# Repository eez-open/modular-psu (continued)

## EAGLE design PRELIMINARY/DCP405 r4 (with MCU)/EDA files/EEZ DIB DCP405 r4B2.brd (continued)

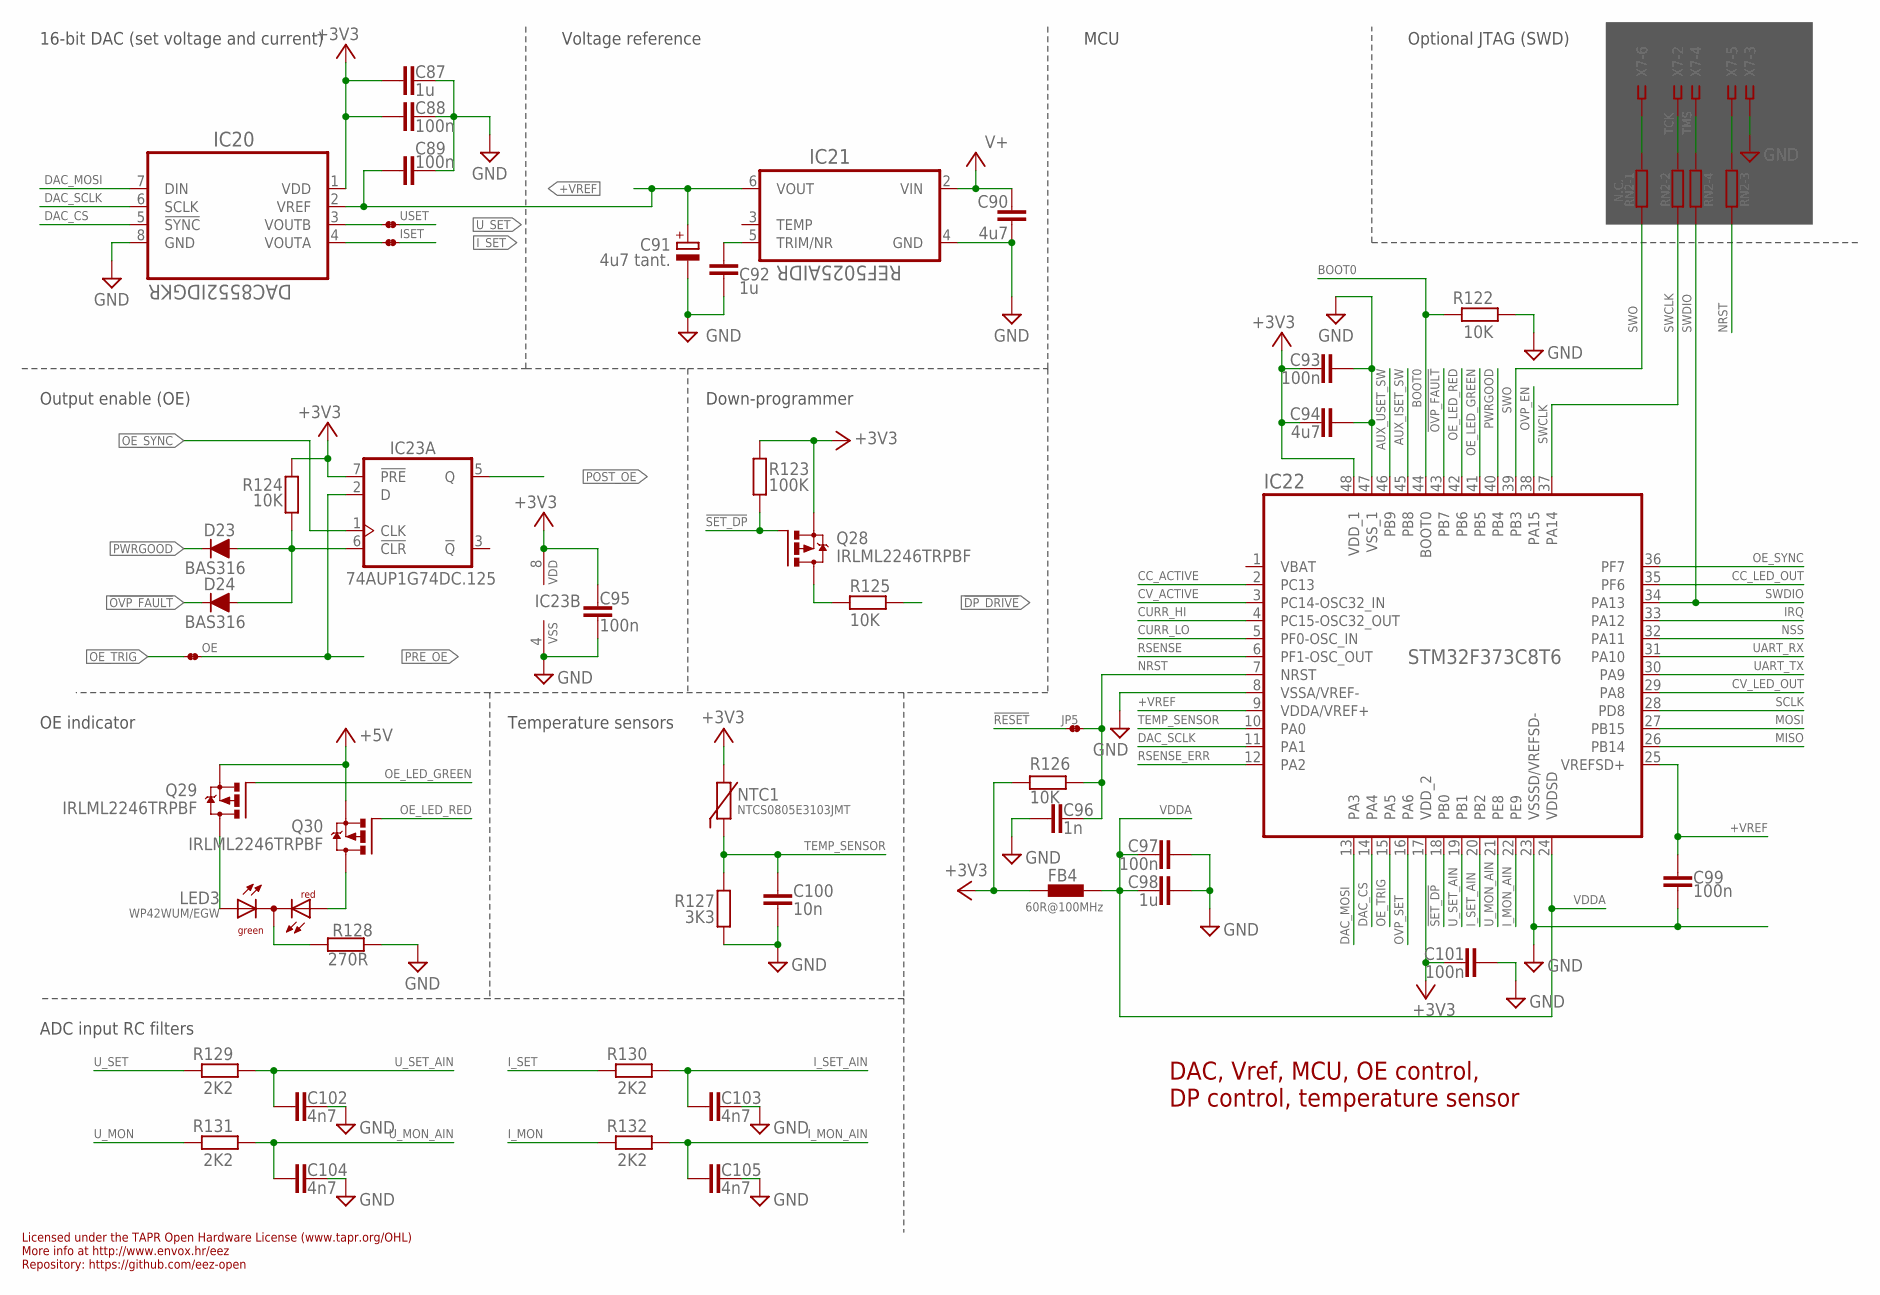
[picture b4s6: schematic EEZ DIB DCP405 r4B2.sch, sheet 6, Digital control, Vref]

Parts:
C87, C92, C98: 1u; C0805
C88, C89, C93, C95, C97, C99, C101: 100n; C0603
C90, C94: 4u7; C1206
C91: 4u7 tant.; EC1206
C96: 1n; C0805
C100: 10n; C0805
C102, C103, C104, C105: 4n7; C0805
D23, D24: BAS316; SOD323-R
FB4: 60R@100MHz; BEAD0603
IC20: DAC8552IDGKR; DGK8-M
IC21: REF5025AIDR; SOIC127P600X175-8N
IC22: STM32F373C8T6; LQFP-48
IC23: 74AUP1G74DC.125; DCU8
ISET: JP2-NOCUT-0805; JP2-0805-NOCUT
JP5: JP2-NOCUT-0805; JP2-0805-NOCUT
LED3: WP42WUM/EGW; L-42WUM-1EGWT
NTC1: NTCS0805E3103JMT; R_0805
OE: JP2-NOCUT-0805; JP2-0805-NOCUT
Q28, Q29, Q30: IRLML2246TRPBF; SOT95P237X112-3N
R122, R124, R125, R126: 10K; R0805
R123: 100K; R0805
R127: 3K3; R0805
R128: 270R; R0805
R129, R130, R131, R132: 2K2; R0805
RN2: N.C.; CAY16
USET: JP2-NOCUT-0805; JP2-0805-NOCUT
X7: N.C.; SSW-106-02-S-S

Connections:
!DP_DRIVE: R125.1; also elsewhere on the board
!OVP_FAULT: D24.C, IC22.43 (PB7); also elsewhere on the board
!RESET: JP5.1; also elsewhere on the board
!SET_DP: IC22.18 (PB0), Q28.1 (G), R123.2
+3V3: C87.1, C88.2, C93.2, C94.1, C95.2, C101.2, FB4.P$1 (1), IC20.1 (VDD), IC22.17 (VDD_2), IC22.48 (VDD_1), IC23.7 (!PRE), IC23.8 (VDD), NTC1.1, Q28.2 (S), R123.1, R124.1, R126.1; also elsewhere on the board
+5V: Q29.2 (S), Q30.2 (S); also elsewhere on the board
+VREF: C89.2, C91.+, C99.2, IC20.2 (VREF), IC21.6 (VOUT), IC22.9 (VDDA/VREF+), IC22.25 (VREFSD+); also elsewhere on the board
AUX_ISET_SW: IC22.45 (PB8); also elsewhere on the board
AUX_USET_SW: IC22.46 (PB9); also elsewhere on the board
BOOT0: IC22.44 (BOOT0), R122.2; also elsewhere on the board
CC_ACTIVE: IC22.2 (PC13); also elsewhere on the board
CC_LED_OUT: IC22.35 (PF6); also elsewhere on the board
CURR_HI: IC22.4 (PC15-OSC32_OUT); also elsewhere on the board
CURR_LO: IC22.5 (PF0-OSC_IN); also elsewhere on the board
CV_ACTIVE: IC22.3 (PC14-OSC32_IN); also elsewhere on the board
CV_LED_OUT: IC22.29 (PA8); also elsewhere on the board
DAC_CS: IC20.5 (!SYNC), IC22.14 (PA4)
DAC_MOSI: IC20.7 (DIN), IC22.13 (PA3)
DAC_SCLK: IC20.6 (SCLK), IC22.11 (PA1)
DP_LED: Q28.3 (D), R125.2
GND: C87.2, C88.1, C89.1, C90.2, C91.-, C92.2, C93.1, C94.2, C95.1, C96.2, C97.1, C98.1, C99.1, C100.1, C101.1, C102.1, C103.1, C104.1, C105.1, IC20.8 (GND), IC21.4 (GND), IC22.8 (VSSA/VREF-), IC22.23 (VSSSD/VREFSD-), IC22.47 (VSS_1), IC23.4 (VSS), R122.1, R127.2, R128.2, X7.3; also elsewhere on the board
IRQ: IC22.33 (PA12); also elsewhere on the board
I_MON: R132.2; also elsewhere on the board
I_MON_AIN: C105.2, IC22.22 (PE9), R132.1
I_SET: ISET.2, R130.2; also elsewhere on the board
I_SET_AIN: C103.2, IC22.20 (PB2), R130.1
MISO: IC22.26 (PB14); also elsewhere on the board
MOSI: IC22.27 (PB15); also elsewhere on the board
unnamed: LED3.CC (C), R128.1
unnamed: LED3.RED (AR), Q30.3 (D)
unnamed: LED3.GREEN (AG), Q29.3 (D)
unnamed: IC20.3 (VOUTB), USET.1
unnamed: IC20.4 (VOUTA), ISET.1
unnamed: D23.A, D24.A, IC23.6 (!CLR), R124.2
unnamed: C92.1, IC21.5 (TRIM/NR)
unnamed: RN2.8 (2), X7.6
unnamed: RN2.6 (2), X7.5
NRST: C96.1, IC22.7 (NRST), JP5.2, R126.2, RN2.3 (1)
NSS: IC22.32 (PA11); also elsewhere on the board
OE_LED_GREEN: IC22.41 (PB5), Q29.1 (G)
OE_LED_RED: IC22.42 (PB6), Q30.1 (G)
OE_SYNC: IC22.36 (PF7), IC23.1 (CLK); also elsewhere on the board
OE_TRIG: IC22.15 (PA5), OE.1
OVP_EN: IC22.38 (PA15); also elsewhere on the board
OVP_SET: IC22.16 (PA6); also elsewhere on the board
POST_OE: IC23.5 (Q); also elsewhere on the board
PRE_OE: IC23.2 (D), OE.2; also elsewhere on the board
PWRGOOD: D23.C, IC22.40 (PB4); also elsewhere on the board
RSENSE: IC22.6 (PF1-OSC_OUT); also elsewhere on the board
RSENSE_ERR: IC22.12 (PA2); also elsewhere on the board
SCLK: IC22.28 (PD8); also elsewhere on the board
SWCLK: IC22.37 (PA14), RN2.2 (1)
SWDIO: IC22.34 (PA13), RN2.4 (1)
SWO: IC22.39 (PB3), RN2.1
TCK: RN2.7 (2), X7.2
TEMP_SENSOR: C100.2, IC22.10 (PA0), NTC1.2, R127.1
TMS: RN2.5 (2), X7.4
UART_RX: IC22.31 (PA10); also elsewhere on the board
UART_TX: IC22.30 (PA9); also elsewhere on the board
U_MON: R131.2; also elsewhere on the board
U_MON_AIN: C104.2, IC22.21 (PE8), R131.1
U_SET: R129.2, USET.2; also elsewhere on the board
U_SET_AIN: C102.2, IC22.19 (PB1), R129.1
V+: C90.1, IC21.2 (VIN); also elsewhere on the board
VDDA: C97.2, C98.2, FB4.P$2 (2), IC22.24 (VDDSD)

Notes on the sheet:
16-bit DAC (set voltage and current)
Voltage reference
Licensed under the TAPR Open Hardware License (www.tapr.org/OHL)
Repository: https://github.com/eez-open
More info at http://www.envox.hr/eez
DAC, Vref, MCU, OE control, DP control, temperature sensor
Down-programmer
Optional JTAG (SWD)
MCU
ADC input RC filters
Temperature sensors
Output enable (OE)
OE indicator

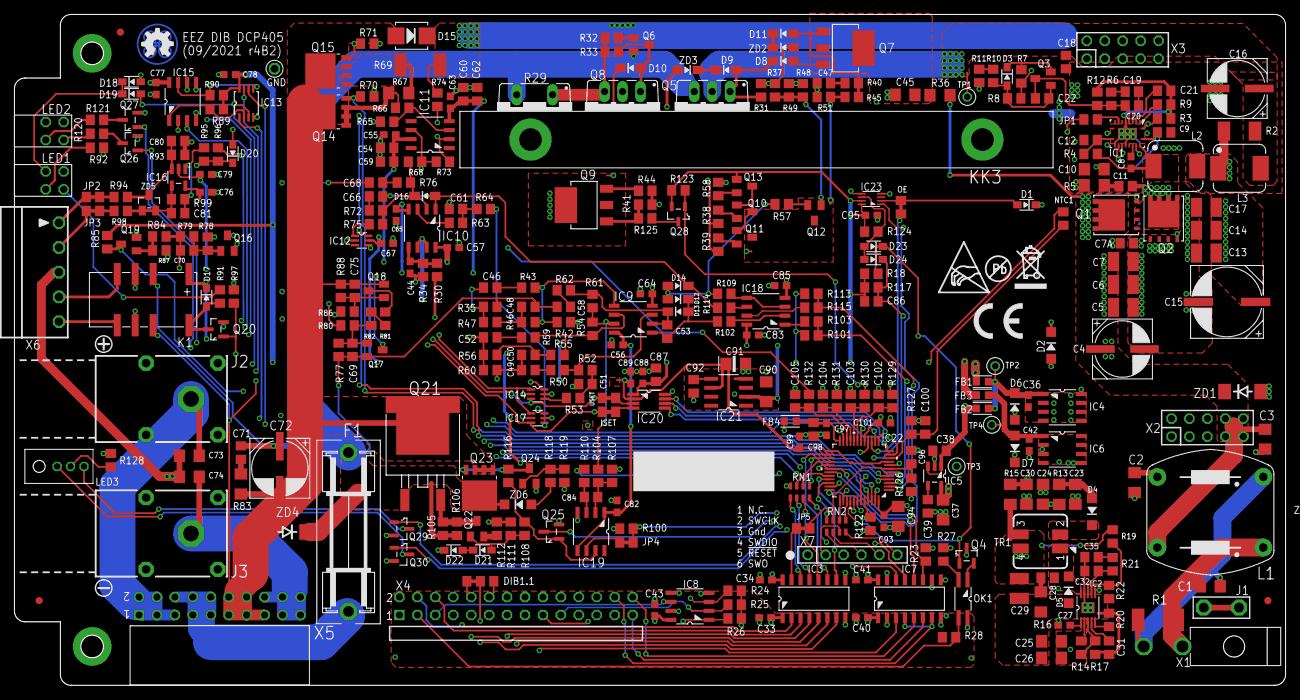
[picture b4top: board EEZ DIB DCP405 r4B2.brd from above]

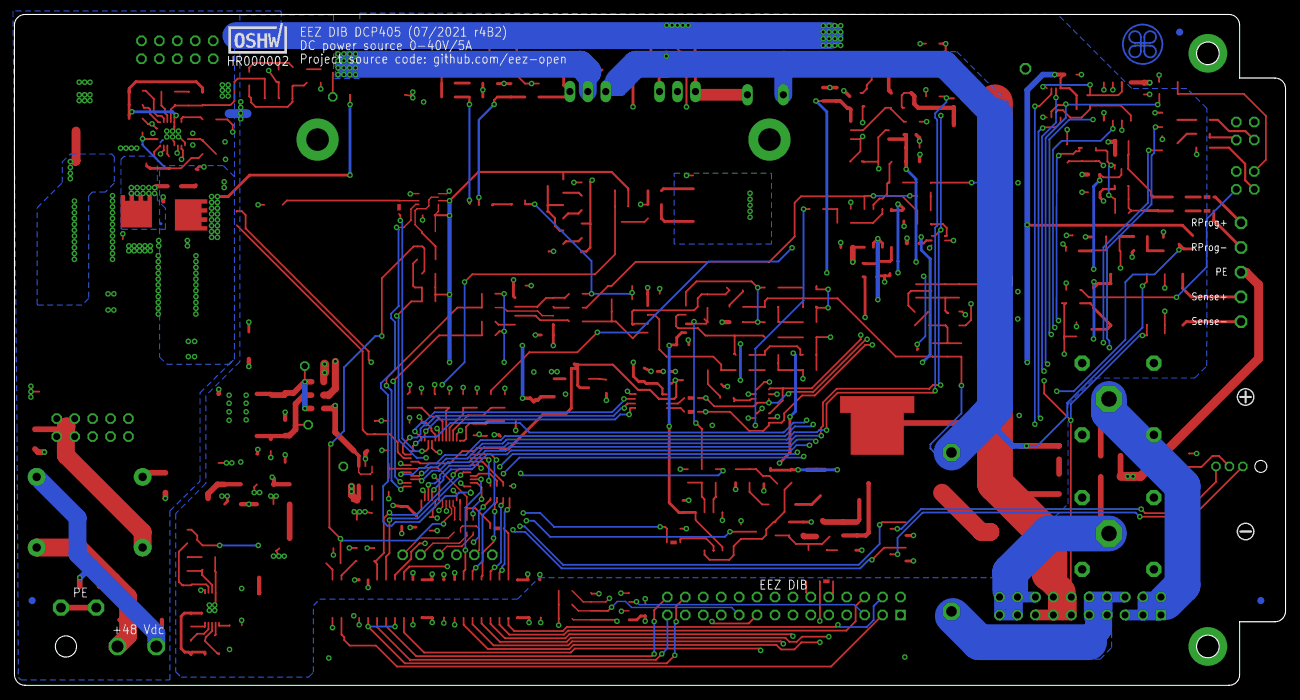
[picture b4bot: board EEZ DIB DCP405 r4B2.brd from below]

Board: 4 copper layers, 180.0 x 95.0 mm, 376 parts (2 on the bottom side), 237 nets.

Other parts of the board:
EEZ_SIGNATURE: SIGNATURESMALL; SIGNATURE_5MM
U$1: RECYCLE_BIN1/8
U$2: CE_5MM
U$6: ESD_SYMBOL
U$7: PB_SMALL

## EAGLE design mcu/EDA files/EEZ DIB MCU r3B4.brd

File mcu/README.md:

### Overview

_IMPORTANT: A crowdfunded version of the MCU module (r2B4) can be found [here](https://github.com/eez-open/modular-psu/tree/master/previous%20designs/mcu%20r2B4%20(Crowd%20Supply%20edition))._

STM32F7 MCU board for controlling up to 3 SPI peripheral modules, I2C fan controller, power soft-start/standby, TFT LCD with resistive touch controller, USB OTG, 10/100 Mbit/s Ethernet, SDRAM, EEPROM, rotary encoder, user switch, speaker and 2+2 digital I/O.

### r3B3 prototype

### Feature list

* [STM32F769IIT6](https://www.st.com/content/st_com/en/products/microcontrollers-microprocessors/stm32-32-bit-arm-cortex-mcus/stm32-high-performance-mcus/stm32f7-series/stm32f7x9/stm32f769ii.html) 32-bit ARM Cortex®-M7 MCU, 216 MHz, 2 MiB Flash, 512 KiB SRAM,  LQFP176 package
* Digital I/O: 2 x buffered inputs and 2 x buffered outputs. Alternative functions: UART, 1 x PWM
* Rotary encoder with switch
* 1 x user switch (use as BOOT0 for firmware loader on power up)
* 3 x SPI channels (2 x Chip selects per channel), 40-pin IDC connector (DIB v1.0)
* Battery backup (CR2032 button cell type)
* AC frequency (50/60 Hz) RTC reference (optional)
* External supervisor with watchdog (optional)
* USB FS, OTG
* Micro SD card
* [DP83848C](https://www.ti.com/product/DP83848C) Ethernet PHY (10/100 Mbit/s)
* 32 KiB I2C EEPROM
* SWG/JTAG connector (optional)
* 8 MiB SDRAM (e.g. [IS42S16400J](https://www.tme.eu/en/details/is42s16400j-7tli/dram-memories-integrated-circuits/issi/)) upgradeable to 32 MiB
* 0.5 mm FFC 40-pin connector for 4.3" TFT LCD 480 x 272 px display
* TFT backlight brightness control
* Resistive touch controller (I2C)
* Soft-start/stand-by control lines for [AUX PS board](https://github.com/eez-open/modular-psu/tree/master/aux-ps)
* Small on-board speaker
* Input power: +5 V (+12 V pass-thru to peripheral modules)
* On board +3.3 V LDO
* Dimensions: 139.5 x 70 mm, 4-layer PCB
* **CE certified design**

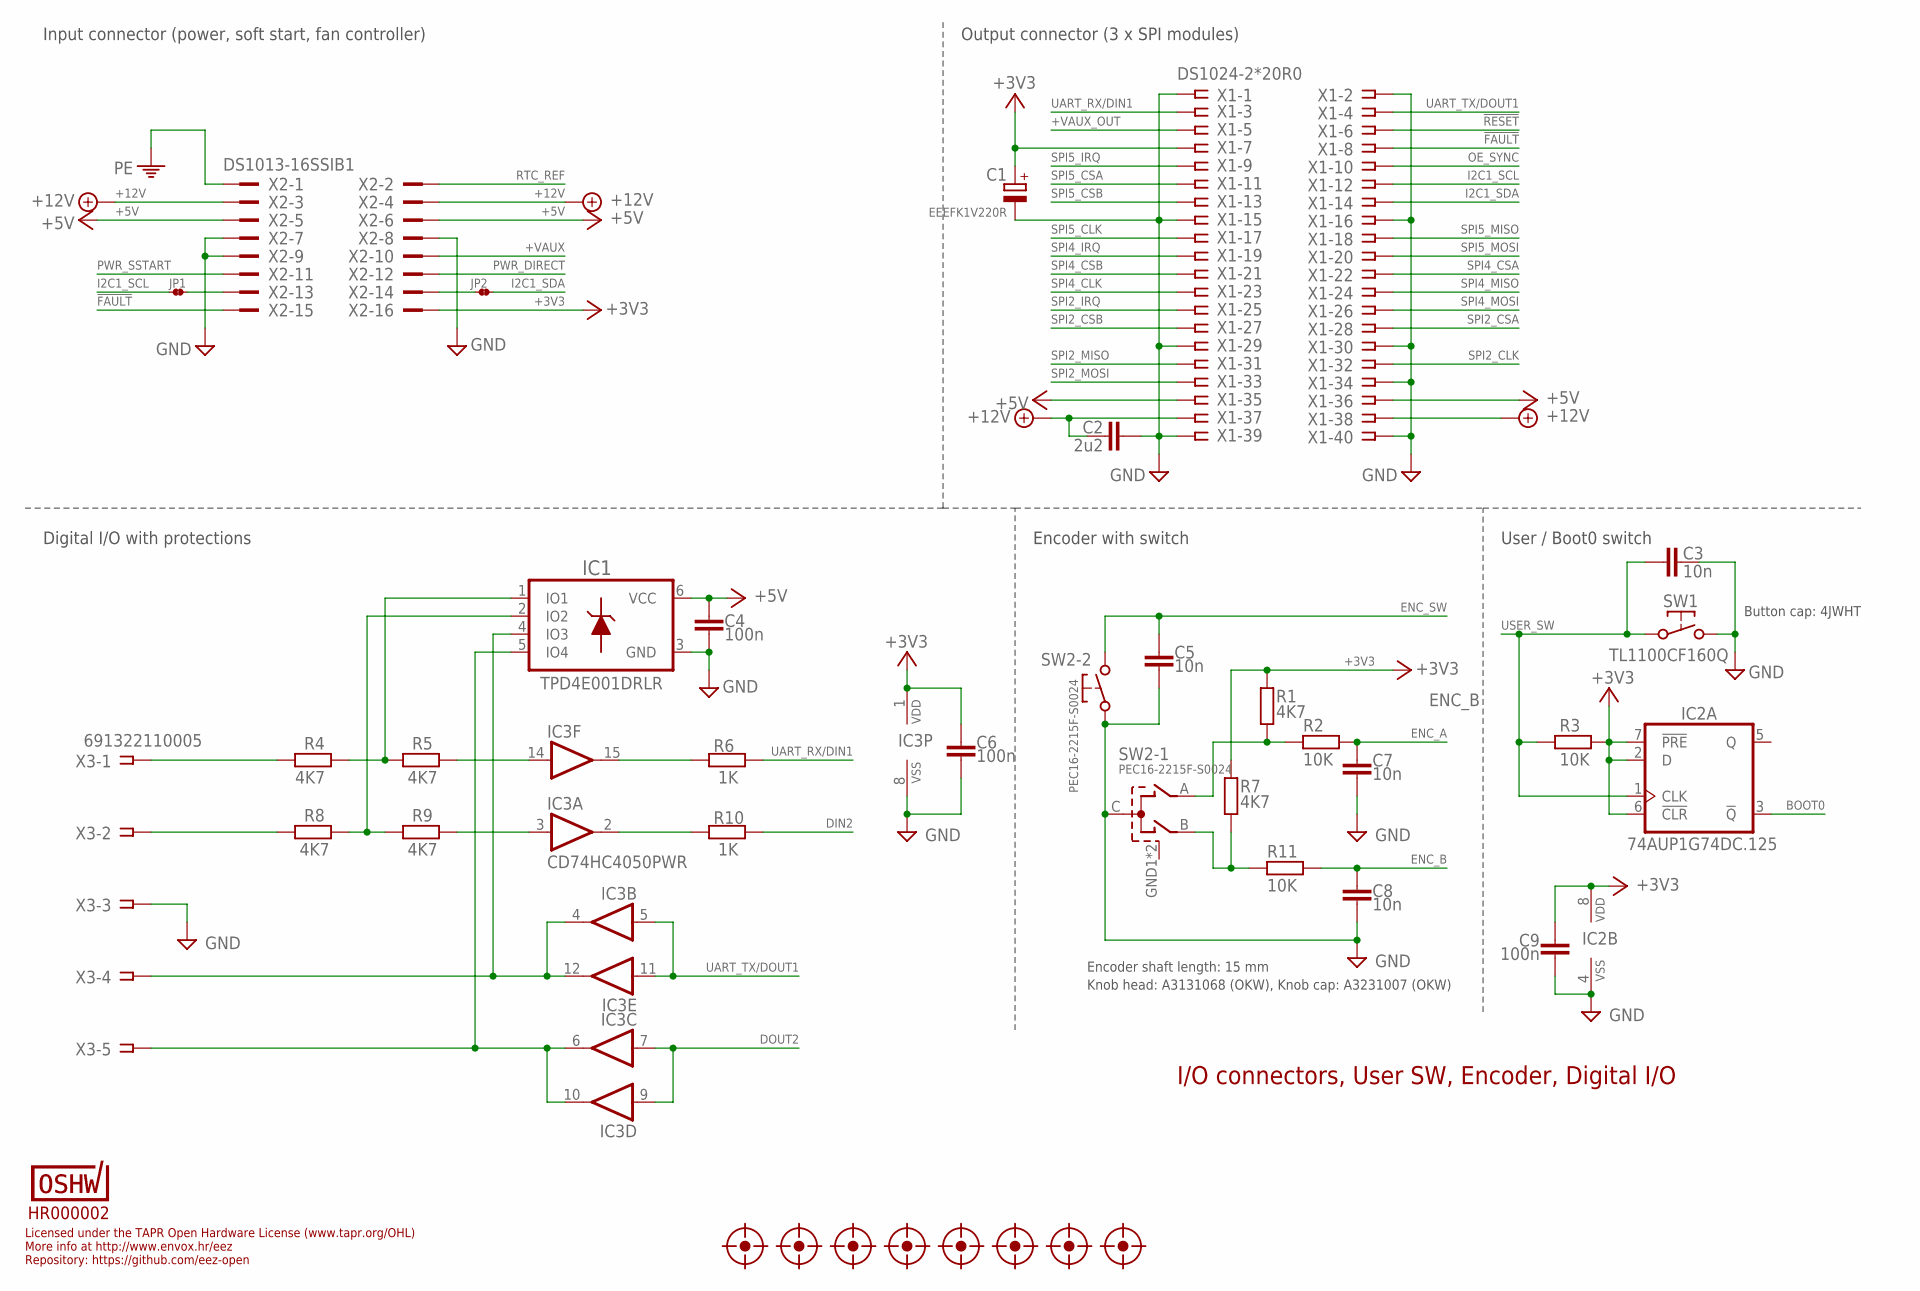
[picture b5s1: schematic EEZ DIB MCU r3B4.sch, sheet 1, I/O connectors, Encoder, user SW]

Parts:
C1: EEEFK1V220R; PANASONIC_C
C2: 2u2; C0805
C3, C5, C7, C8: 10n; C0805
C4, C6, C9: 100n; C0603
FM1, FM2, FM3, FM4, FM5, FM6, FM7, FM8: FIDUCIAL
IC1: TPD4E001DRLR; DRL6
IC2: 74AUP1G74DC.125; DCU8
IC3: CD74HC4050PWR; PW16
JP1, JP2: JP2-NOCUT
LABEL1: HR000002; CERT-SMALL-SILK
R1, R4, R5, R7, R8, R9: 4K7; R0805
R2, R3, R11: 10K; R0805
R6, R10: 1K; R0805
SW1: TL1100CF160Q; TL1100C
SW2: PEC16-2215F-S0024; PEC16-2215F
X1: DS1024-2*20R0; ZL263-40DG
X2: DS1013-16SSIB1; IDC-16PIN
X3: 691322110005; MC1,5/5-G-3,5

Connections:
!FAULT: X1.8, X2.15; also elsewhere on the board
!RESET: X1.6; also elsewhere on the board
+3V3: C1.1 (+), C6.1, C9.1, IC2.2 (D), IC2.6 (!CLR), IC2.7 (!PRE), IC2.8 (VDD), IC3.1 (VDD), R1.1, R3.1, R7.1, X1.7, X2.16; also elsewhere on the board
+5V: C4.1, IC1.6 (VCC), X1.35, X1.36, X2.5, X2.6; also elsewhere on the board
+12V: C2.1, X1.37, X1.38, X2.3, X2.4
+VAUX: X2.10; also elsewhere on the board
+VAUX_OUT: X1.5; also elsewhere on the board
BOOT0: IC2.3 (!Q); also elsewhere on the board
DIN2: R10.2; also elsewhere on the board
DOUT2: IC3.7 (I), IC3.9 (I); also elsewhere on the board
ENC_A: C7.2, R2.1; also elsewhere on the board
ENC_B: C8.1, R11.1; also elsewhere on the board
ENC_SW: C5.2, SW2.E (2); also elsewhere on the board
EOUT_A: R1.2, R2.2, SW2.A
EOUT_B: R7.2, R11.2, SW2.B
GND: C1.2 (-), C2.2, C3.1, C4.2, C5.1, C6.2, C7.1, C8.2, C9.2, IC1.3 (GND), IC2.4 (VSS), IC3.8 (VSS), SW1.2, SW2.C, SW2.D (1), X1.1, X1.2, X1.15, X1.16, X1.29, X1.30, X1.34, X1.39, X1.40, X2.7, X2.8, X2.9, X3.3; also elsewhere on the board
I2C1_SCL: JP1.1, X1.12; also elsewhere on the board
I2C1_SDA: JP2.2, X1.14; also elsewhere on the board
unnamed: JP1.2, X2.13
unnamed: JP2.1, X2.14
unnamed: IC1.2 (IO2), R8.2, R9.1
unnamed: IC3.15 (O), R6.1
unnamed: IC3.2 (O), R10.1
unnamed: IC3.14 (I), R5.2
unnamed: IC3.3 (I), R9.2
unnamed: R4.1, X3.1
OE_SYNC: X1.10; also elsewhere on the board
PE: X2.1; also elsewhere on the board
PWR_DIRECT: X2.12; also elsewhere on the board
PWR_SSTART: X2.11; also elsewhere on the board
RTC_REF: X2.2; also elsewhere on the board
SPI2_CLK: X1.32; also elsewhere on the board
SPI2_CSA: X1.28; also elsewhere on the board
SPI2_CSB: X1.27; also elsewhere on the board
SPI2_IRQ: X1.25; also elsewhere on the board
SPI2_MISO: X1.31; also elsewhere on the board
SPI2_MOSI: X1.33; also elsewhere on the board
SPI4_CLK: X1.23; also elsewhere on the board
SPI4_CSA: X1.22; also elsewhere on the board
SPI4_CSB: X1.21; also elsewhere on the board
SPI4_IRQ: X1.19; also elsewhere on the board
SPI4_MISO: X1.24; also elsewhere on the board
SPI4_MOSI: X1.26; also elsewhere on the board
SPI5_CLK: X1.17; also elsewhere on the board
SPI5_CSA: X1.11; also elsewhere on the board
SPI5_CSB: X1.13; also elsewhere on the board
SPI5_IRQ: X1.9; also elsewhere on the board
SPI5_MISO: X1.18; also elsewhere on the board
SPI5_MOSI: X1.20; also elsewhere on the board
UART_RX/DIN1: R6.2, X1.3; also elsewhere on the board
UART_TX/DOUT1: IC3.5 (I), IC3.11 (I), X1.4; also elsewhere on the board
USER_SW: C3.2, IC2.1 (CLK), R3.2, SW1.1; also elsewhere on the board
X_DIN1: IC1.1 (IO1), R4.2, R5.1
X_DIN2: R8.1, X3.2
X_DOUT1: IC1.4 (IO3), IC3.4 (O), IC3.12 (O), X3.4
X_DOUT2: IC1.5 (IO4), IC3.6 (O), IC3.10 (O), X3.5

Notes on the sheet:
Licensed under the TAPR Open Hardware License (www.tapr.org/OHL)
Repository: https://github.com/eez-open
More info at http://www.envox.hr/eez
Encoder shaft length: 15 mm
Knob head: A3131068 (OKW), Knob cap: A3231007 (OKW)
I/O connectors, User SW, Encoder, Digital I/O
Digital I/O with protections
Encoder with switch
User / Boot0 switch
Input connector (power, soft start, fan controller)
Output connector (3 x SPI modules)
Button cap: 4JWHT

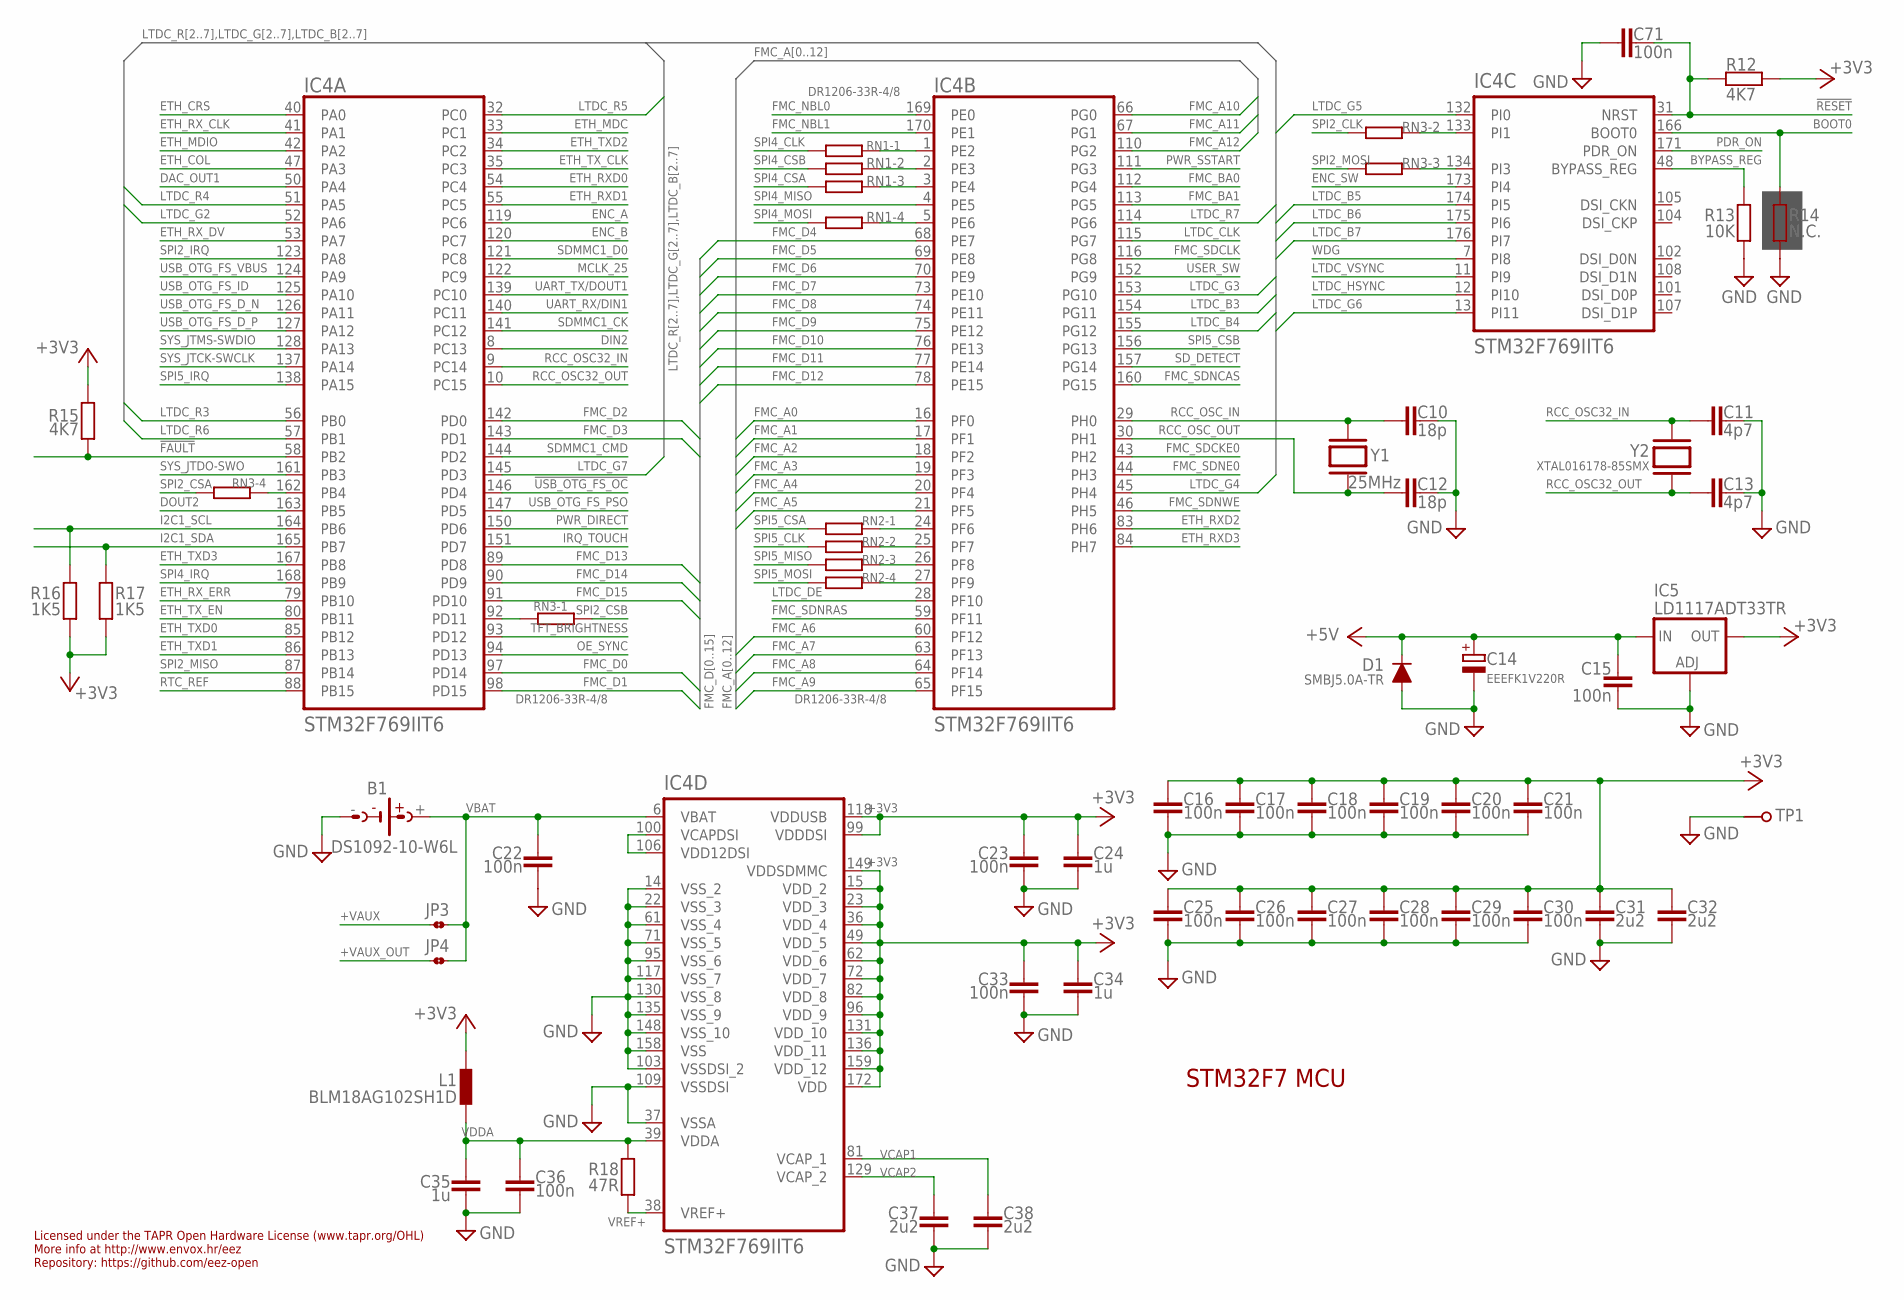
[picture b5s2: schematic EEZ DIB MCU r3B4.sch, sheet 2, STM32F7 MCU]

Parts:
B1: DS1092-10-W6L
C10, C12: 18p; C0603
C11, C13: 4p7; C0603
C14: EEEFK1V220R; PANASONIC_C
C15, C16, C17, C18, C19, C20, C21, C22, C23, C25, C26, C27, C28, C29, C30, C33, C36, C71: 100n; C0603
C24, C34, C35: 1u; C0805
C31, C32, C37, C38: 2u2; C0805
D1: SMBJ5.0A-TR; DO214AA
IC4: STM32F769IIT6; LQFP-176_24X24MM
IC5: LD1117ADT33TR; DPACK
JP3, JP4: JP2-CUT-0805; R_0805
L1: BLM18AG102SH1D; BEAD0603
R12, R15: 4K7; R0805
R13: 10K; R0805
R14: N.C.; R0805
R16, R17: 1K5; R0805
R18: 47R; R0805
RN1, RN2, RN3: DR1206-33R-4/8; CAY16
TP1: PCB_TEST_TABSHIELD; PCB_SHIELD_TAB
Y1: 25MHz; HC-49/4H
Y2: XTAL016178-85SMX; 85SMX

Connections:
!FAULT: IC4.58 (PB2), R15.2; also elsewhere on the board
!RESET: C71.2, IC4.31 (NRST), R12.2; also elsewhere on the board
!USB_OTG_FS_OC: IC4.146 (PD4); also elsewhere on the board
+3V3: C16.1, C17.1, C18.1, C19.1, C20.1, C21.1, C23.1, C24.1, C25.1, C26.1, C27.1, C28.1, C29.1, C30.1, C31.1, C32.1, C33.1, C34.1, IC4.15 (VDD_2), IC4.23 (VDD_3), IC4.36 (VDD_4), IC4.49 (VDD_5), IC4.62 (VDD_6), IC4.72 (VDD_7), IC4.82 (VDD_8), IC4.96 (VDD_9), IC4.99 (VDDDSI), IC4.118 (VDDUSB), IC4.131 (VDD_10), IC4.136 (VDD_11), IC4.149 (VDDSDMMC), IC4.159 (VDD_12), IC4.172 (VDD), IC5.4 (OUT), L1.P$1 (1), R12.1, R15.1, R16.1, R17.1; also elsewhere on the board
+5V: C14.1 (+), C15.1, D1.C, IC5.3 (IN); also elsewhere on the board
+VAUX: JP3.2; also elsewhere on the board
+VAUX_OUT: JP4.2; also elsewhere on the board
BOOT0: IC4.166 (BOOT0), R14.2; also elsewhere on the board
BYPASS_REG: IC4.48 (BYPASS_REG), R13.2
DAC_OUT1: IC4.50 (PA4); also elsewhere on the board
DIN2: IC4.8 (PC13); also elsewhere on the board
DOUT2: IC4.163 (PB5); also elsewhere on the board
ENC_A: IC4.119 (PC6); also elsewhere on the board
ENC_B: IC4.120 (PC7); also elsewhere on the board
ENC_SW: IC4.173 (PI4); also elsewhere on the board
ETH_COL: IC4.47 (PA3); also elsewhere on the board
ETH_CRS: IC4.40 (PA0); also elsewhere on the board
ETH_MDC: IC4.33 (PC1); also elsewhere on the board
ETH_MDIO: IC4.42 (PA2); also elsewhere on the board
ETH_RXD0: IC4.54 (PC4); also elsewhere on the board
ETH_RXD1: IC4.55 (PC5); also elsewhere on the board
ETH_RXD2: IC4.83 (PH6); also elsewhere on the board
ETH_RXD3: IC4.84 (PH7); also elsewhere on the board
ETH_RX_CLK: IC4.41 (PA1); also elsewhere on the board
ETH_RX_DV: IC4.53 (PA7); also elsewhere on the board
ETH_RX_ERR: IC4.79 (PB10); also elsewhere on the board
ETH_TXD0: IC4.85 (PB12); also elsewhere on the board
ETH_TXD1: IC4.86 (PB13); also elsewhere on the board
ETH_TXD2: IC4.34 (PC2); also elsewhere on the board
ETH_TXD3: IC4.167 (PB8); also elsewhere on the board
ETH_TX_CLK: IC4.35 (PC3); also elsewhere on the board
ETH_TX_EN: IC4.80 (PB11); also elsewhere on the board
FMC_A0: IC4.16 (PF0); also elsewhere on the board
FMC_A1: IC4.17 (PF1); also elsewhere on the board
FMC_A2: IC4.18 (PF2); also elsewhere on the board
FMC_A3: IC4.19 (PF3); also elsewhere on the board
FMC_A4: IC4.20 (PF4); also elsewhere on the board
FMC_A5: IC4.21 (PF5); also elsewhere on the board
FMC_A6: IC4.60 (PF12); also elsewhere on the board
FMC_A7: IC4.63 (PF13); also elsewhere on the board
FMC_A8: IC4.64 (PF14); also elsewhere on the board
FMC_A9: IC4.65 (PF15); also elsewhere on the board
FMC_A10: IC4.66 (PG0); also elsewhere on the board
FMC_A11: IC4.67 (PG1); also elsewhere on the board
FMC_A12: IC4.110 (PG2); also elsewhere on the board
FMC_BA0: IC4.112 (PG4); also elsewhere on the board
FMC_BA1: IC4.113 (PG5); also elsewhere on the board
FMC_D0: IC4.97 (PD14); also elsewhere on the board
FMC_D1: IC4.98 (PD15); also elsewhere on the board
FMC_D2: IC4.142 (PD0); also elsewhere on the board
FMC_D3: IC4.143 (PD1); also elsewhere on the board
FMC_D4: IC4.68 (PE7); also elsewhere on the board
FMC_D5: IC4.69 (PE8); also elsewhere on the board
FMC_D6: IC4.70 (PE9); also elsewhere on the board
FMC_D7: IC4.73 (PE10); also elsewhere on the board
FMC_D8: IC4.74 (PE11); also elsewhere on the board
FMC_D9: IC4.75 (PE12); also elsewhere on the board
FMC_D10: IC4.76 (PE13); also elsewhere on the board
FMC_D11: IC4.77 (PE14); also elsewhere on the board
FMC_D12: IC4.78 (PE15); also elsewhere on the board
FMC_D13: IC4.89 (PD8); also elsewhere on the board
FMC_D14: IC4.90 (PD9); also elsewhere on the board
FMC_D15: IC4.91 (PD10); also elsewhere on the board
FMC_NBL0: IC4.169 (PE0); also elsewhere on the board
FMC_NBL1: IC4.170 (PE1); also elsewhere on the board
FMC_SDCKE0: IC4.43 (PH2); also elsewhere on the board
FMC_SDCLK: IC4.116 (PG8); also elsewhere on the board
FMC_SDNCAS: IC4.160 (PG15); also elsewhere on the board
FMC_SDNE0: IC4.44 (PH3); also elsewhere on the board
FMC_SDNRAS: IC4.59 (PF11); also elsewhere on the board
FMC_SDNWE: IC4.46 (PH5); also elsewhere on the board
GND: B1.-, C10.1, C11.2, C12.1, C13.2, C14.2 (-), C15.2, C16.2, C17.2, C18.2, C19.2, C20.2, C21.2, C22.2, C23.2, C24.2, C25.2, C26.2, C27.2, C28.2, C29.2, C30.2, C31.2, C32.2, C33.2, C34.2, C35.2, C36.2, C37.2, C38.2, C71.1, D1.A, IC4.14 (VSS_2), IC4.22 (VSS_3), IC4.37 (VSSA), IC4.61 (VSS_4), IC4.71 (VSS_5), IC4.95 (VSS_6), IC4.103 (VSSDSI_2), IC4.109 (VSSDSI), IC4.117 (VSS_7), IC4.130 (VSS_8), IC4.135 (VSS_9), IC4.148 (VSS_10), IC4.158 (VSS), IC5.1 (ADJ), R13.1, R14.1, TP1.1; also elsewhere on the board
I2C1_SCL: IC4.164 (PB6), R16.2; also elsewhere on the board
I2C1_SDA: IC4.165 (PB7), R17.2; also elsewhere on the board
IRQ_TOUCH: IC4.151 (PD7); also elsewhere on the board
LTDC_B3: IC4.154 (PG11); also elsewhere on the board
LTDC_B4: IC4.155 (PG12); also elsewhere on the board
LTDC_B5: IC4.174 (PI5); also elsewhere on the board
LTDC_B6: IC4.175 (PI6); also elsewhere on the board
LTDC_B7: IC4.176 (PI7); also elsewhere on the board
LTDC_CLK: IC4.115 (PG7); also elsewhere on the board
LTDC_DE: IC4.28 (PF10); also elsewhere on the board
LTDC_G2: IC4.52 (PA6); also elsewhere on the board
LTDC_G3: IC4.153 (PG10); also elsewhere on the board
LTDC_G4: IC4.45 (PH4); also elsewhere on the board
LTDC_G5: IC4.132 (PI0); also elsewhere on the board
LTDC_G6: IC4.13 (PI11); also elsewhere on the board
LTDC_G7: IC4.145 (PD3); also elsewhere on the board
LTDC_HSYNC: IC4.12 (PI10); also elsewhere on the board
LTDC_R3: IC4.56 (PB0); also elsewhere on the board
LTDC_R4: IC4.51 (PA5); also elsewhere on the board
LTDC_R5: IC4.32 (PC0); also elsewhere on the board
LTDC_R6: IC4.57 (PB1); also elsewhere on the board
LTDC_R7: IC4.114 (PG6); also elsewhere on the board
LTDC_VSYNC: IC4.11 (PI9); also elsewhere on the board
MCLK_25: IC4.122 (PC9); also elsewhere on the board
unnamed: IC4.24 (PF6), RN2.8 (2)
unnamed: IC4.25 (PF7), RN2.7 (2)
unnamed: IC4.26 (PF8), RN2.6 (2)
unnamed: IC4.27 (PF9), RN2.5 (2)
unnamed: IC4.1 (PE2), RN1.8 (2)
unnamed: IC4.2 (PE3), RN1.7 (2)
unnamed: IC4.3 (PE4), RN1.6 (2)
unnamed: IC4.5 (PE6), RN1.5 (2)
unnamed: IC4.92 (PD11), RN3.8 (2)
unnamed: IC4.162 (PB4), RN3.5 (2)
unnamed: IC4.133 (PI1), RN3.7 (2)
unnamed: IC4.134 (PI3), RN3.6 (2)
unnamed: IC4.100 (VCAPDSI), IC4.106 (VDD12DSI)
OE_SYNC: IC4.94 (PD13); also elsewhere on the board
PDR_ON: IC4.171 (PDR_ON); also elsewhere on the board
PWR_DIRECT: IC4.150 (PD6); also elsewhere on the board
PWR_SSTART: IC4.111 (PG3); also elsewhere on the board
RCC_OSC32_IN: C11.1, IC4.9 (PC14), Y2.1
RCC_OSC32_OUT: C13.1, IC4.10 (PC15), Y2.4 (2)
RCC_OSC_IN: C10.2, IC4.29 (PH0), Y1.2
RCC_OSC_OUT: C12.2, IC4.30 (PH1), Y1.1
RTC_REF: IC4.88 (PB15); also elsewhere on the board
SDMMC1_CK: IC4.141 (PC12); also elsewhere on the board
SDMMC1_CMD: IC4.144 (PD2); also elsewhere on the board
SDMMC1_D0: IC4.121 (PC8); also elsewhere on the board
SD_DETECT: IC4.157 (PG14); also elsewhere on the board
SPI2_CLK: RN3.2 (1); also elsewhere on the board
SPI2_CSA: RN3.4 (1); also elsewhere on the board
SPI2_CSB: RN3.1; also elsewhere on the board
SPI2_IRQ: IC4.123 (PA8); also elsewhere on the board
SPI2_MISO: IC4.87 (PB14); also elsewhere on the board
SPI2_MOSI: RN3.3 (1); also elsewhere on the board
SPI4_CLK: RN1.1; also elsewhere on the board
SPI4_CSA: RN1.3 (1); also elsewhere on the board
SPI4_CSB: RN1.2 (1); also elsewhere on the board
SPI4_IRQ: IC4.168 (PB9); also elsewhere on the board
SPI4_MISO: IC4.4 (PE5); also elsewhere on the board
SPI4_MOSI: RN1.4 (1); also elsewhere on the board
SPI5_CLK: RN2.2 (1); also elsewhere on the board
SPI5_CSA: RN2.1; also elsewhere on the board
SPI5_CSB: IC4.156 (PG13); also elsewhere on the board
SPI5_IRQ: IC4.138 (PA15); also elsewhere on the board
SPI5_MISO: RN2.3 (1); also elsewhere on the board
SPI5_MOSI: RN2.4 (1); also elsewhere on the board
SYS_JTCK-SWCLK: IC4.137 (PA14); also elsewhere on the board
SYS_JTDO-SWO: IC4.161 (PB3); also elsewhere on the board
SYS_JTMS-SWDIO: IC4.128 (PA13); also elsewhere on the board
TFT_BRIGHTNESS: IC4.93 (PD12); also elsewhere on the board
UART_RX/DIN1: IC4.140 (PC11); also elsewhere on the board
UART_TX/DOUT1: IC4.139 (PC10); also elsewhere on the board
USB_OTG_FS_D_N: IC4.126 (PA11); also elsewhere on the board
USB_OTG_FS_D_P: IC4.127 (PA12); also elsewhere on the board
USB_OTG_FS_ID: IC4.125 (PA10); also elsewhere on the board
USB_OTG_FS_PSO: IC4.147 (PD5); also elsewhere on the board
USB_OTG_FS_VBUS: IC4.124 (PA9); also elsewhere on the board
USER_SW: IC4.152 (PG9); also elsewhere on the board
VBAT: B1.+, C22.1, IC4.6 (VBAT), JP3.1, JP4.1
VCAP1: C38.1, IC4.81 (VCAP_1)
VCAP2: C37.1, IC4.129 (VCAP_2)
VDDA: C35.1, C36.1, IC4.39 (VDDA), L1.P$2 (2), R18.2
VREF+: IC4.38 (VREF+), R18.1
WDG: IC4.7 (PI8); also elsewhere on the board

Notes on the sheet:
Licensed under the TAPR Open Hardware License (www.tapr.org/OHL)
Repository: https://github.com/eez-open
More info at http://www.envox.hr/eez
STM32F7 MCU
